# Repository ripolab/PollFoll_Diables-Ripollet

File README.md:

# PollFoll dels Diables de Ripollet
Projecte de col.laboració amb els Diables de Ripollet.
Record del 20è Aniversari Poll Foll

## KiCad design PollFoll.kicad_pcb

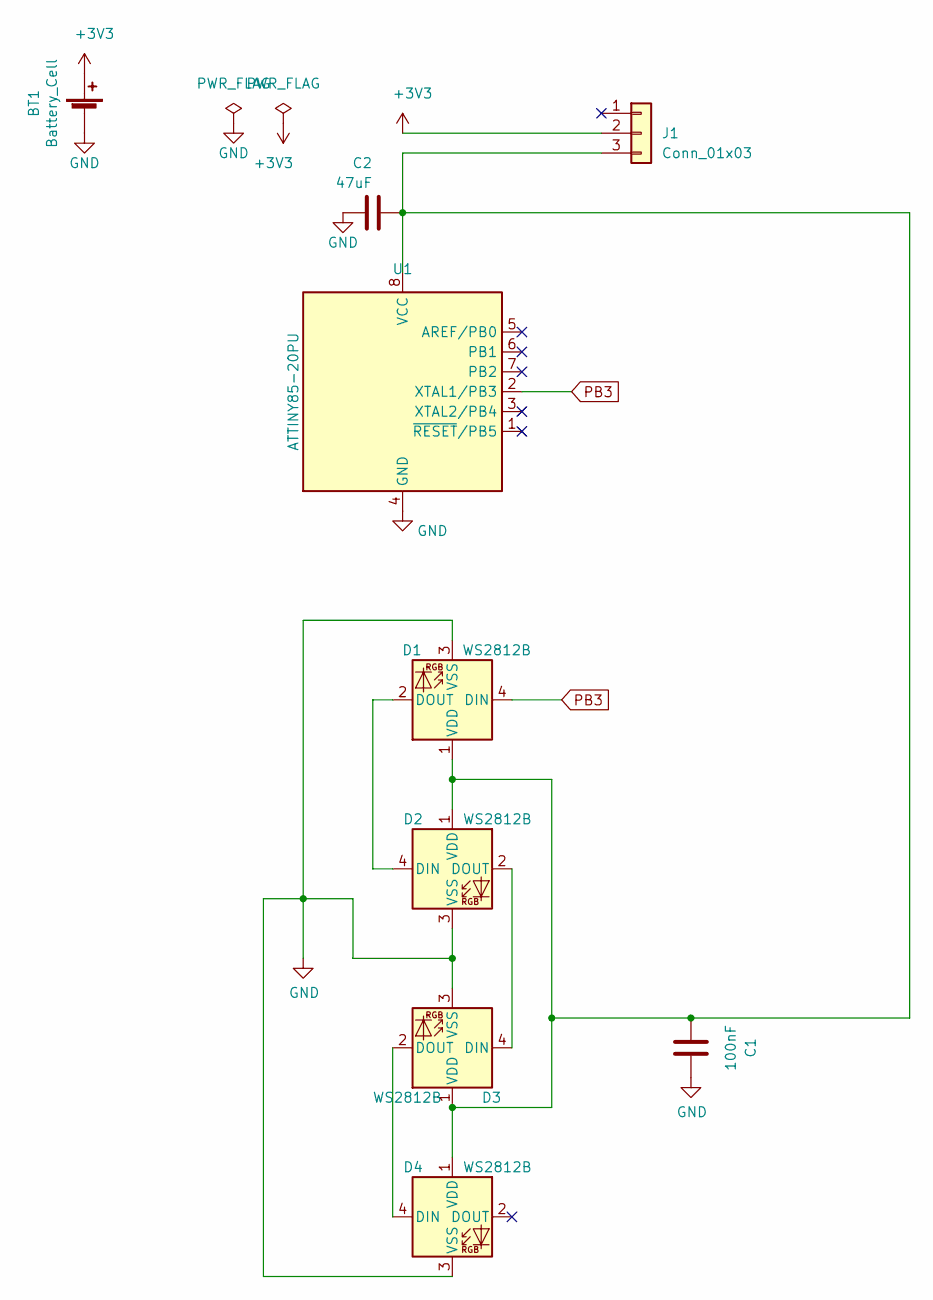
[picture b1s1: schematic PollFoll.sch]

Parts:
BT1: Battery_Cell; BatteryHolder_Keystone_3034_1x20mm_MODIFICADA
C1: 100nF; C_0805_2012Metric_Pad1.15x1.40mm_HandSolder
C2: 47uF; C_0805_2012Metric_Pad1.15x1.40mm_HandSolder
D1, D2, D3, D4: WS2812B; LED_WS2812B_PLCC4_5.0x5.0mm_P3.2mm
J1: Conn_01x03; PinHeader_1x03_P2.54mm_Vertical
U1: ATTINY85-20PU; DIP-8_W7.62mm

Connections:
+3V3: BT1.1 (+), J1.2
GND: BT1.2 (-), C1.2, C2.1, D1.3 (VSS), D2.3 (VSS), D3.3 (VSS), D4.3 (VSS), U1.4 (GND)
unnamed: C1.1, C2.2, D1.1 (VDD), D2.1 (VDD), D3.1 (VDD), D4.1 (VDD), J1.3, U1.8 (VCC)
unnamed: D1.2 (DOUT), D2.4 (DIN)
unnamed: D2.2 (DOUT), D3.4 (DIN)
unnamed: D3.2 (DOUT), D4.4 (DIN)
PB3: D1.4 (DIN), U1.2 (XTAL1/PB3)

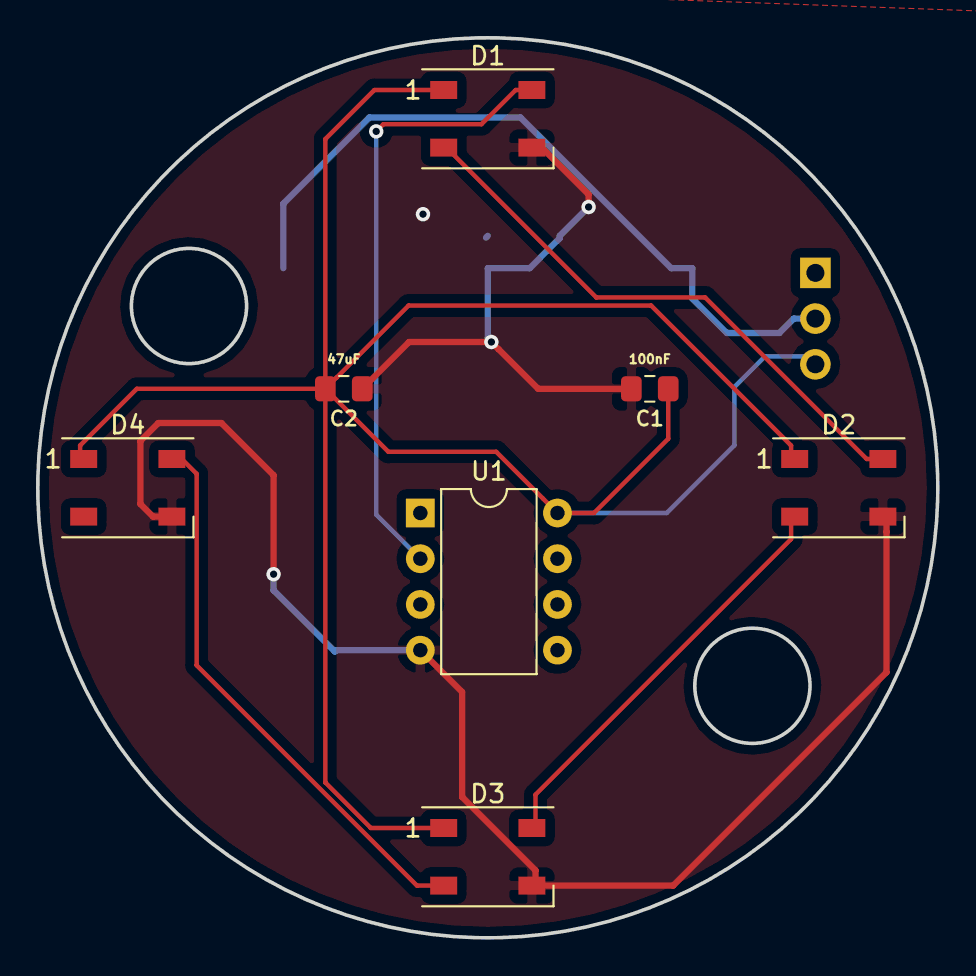
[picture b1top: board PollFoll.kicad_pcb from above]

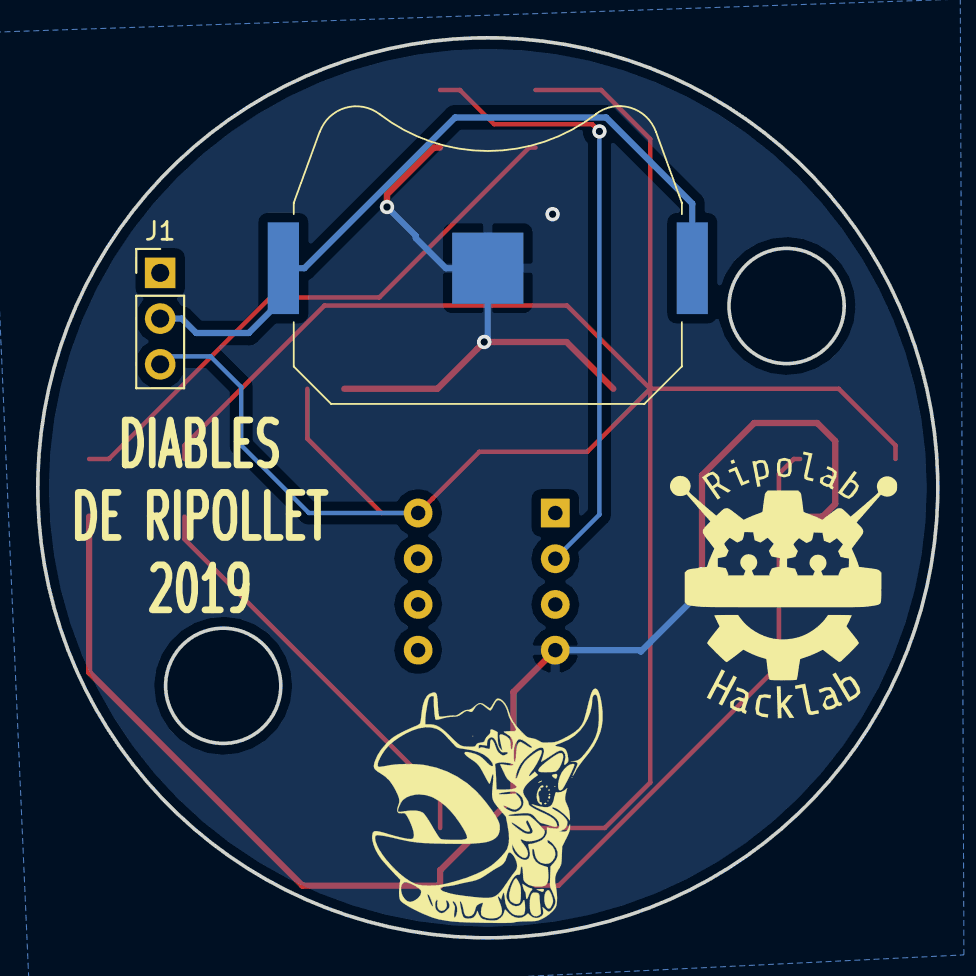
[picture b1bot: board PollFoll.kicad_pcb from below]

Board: 2 copper layers, 50.0 x 50.0 mm, 11 parts (3 on the bottom side), 7 nets.

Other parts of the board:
Ref**: Val**; pollfoll
svg2mod: G***; logo_ripolab_12x14mm
